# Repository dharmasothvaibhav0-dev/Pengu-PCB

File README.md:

# Pengu-PCB
Using an Astable Multivibrator to light up different LEDS automatically, the LEDS as the eyes oscillate and flash after one another (Like they are winking)

-----------------------------------------------------------------------------------------
# The Circuit

The Main components in my circuit includes 6 resistors, 2 capacitors, 2 transistors, and 8 LEDS. The circuit itself is basically an Astable multivibrator which is what causes the oscillation to occur. I originally intended to create a seperate Bistable multivibrator, however it did not work as expected so I connected the components from the bistable to create one big Astable circuit. Because of the Astable circuit type, it causes the LEDS to flash one after another in a pattern. An observation I made was that the pattern for the bottom LEDS can also swap if we were to reroute the wires to the opposite collector which was interesting to me. 

----------------------------------------------------------------------------------------------------
# The Schematic

--------------------------------------------------------------------------------------------------
# Falstad Circuit link

I created the circuit using Falstad. Feel free to try it out!

https://is.gd/EEGnGU

------------------------------------------------------------------------------------------------

# PCB Design

I chose to convert my Circuit into the design of a penguin. I used the main two LEDS part of the Astable circuit as the eyes for the penguin, and the other LEDS I attached as arms.

Front of the PCB- 

Back of the PCB-

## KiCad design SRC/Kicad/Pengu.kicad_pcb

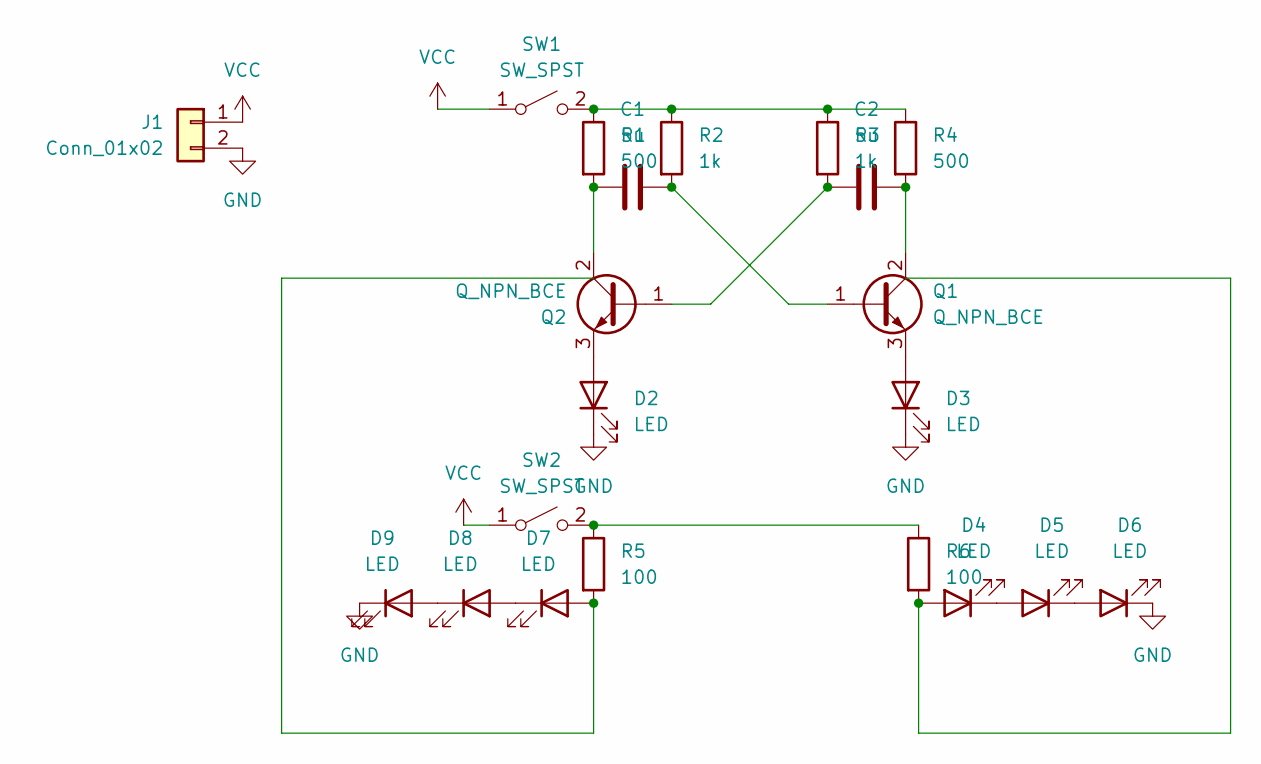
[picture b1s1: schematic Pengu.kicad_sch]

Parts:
C1, C2: 5u; C_Disc_D5.0mm_W2.5mm_P5.00mm
D2, D3, D4, D5, D6, D7, D8, D9: LED; LED_D5.0mm
J1: Conn_01x02; PinHeader_1x02_P2.54mm_Vertical
Q1, Q2: Q_NPN_BCE; TO-92L_Inline_Wide
R1, R4: 500; R_Axial_DIN0204_L3.6mm_D1.6mm_P7.62mm_Horizontal
R2, R3: 1k; R_Axial_DIN0204_L3.6mm_D1.6mm_P7.62mm_Horizontal
R5, R6: 100; R_Axial_DIN0204_L3.6mm_D1.6mm_P7.62mm_Horizontal
SW1, SW2: SW_SPST; SW_PUSH_6mm

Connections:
GND: D2.1 (K), D3.1 (K), D6.1 (K), D9.1 (K), J1.2
unnamed: D2.2 (A), Q2.3 (E)
unnamed: D3.2 (A), Q1.3 (E)
unnamed: D4.2 (A), R6.2
unnamed: D4.1 (K), D5.2 (A)
unnamed: D5.1 (K), D6.2 (A)
unnamed: D7.2 (A), R5.2
unnamed: D7.1 (K), D8.2 (A)
unnamed: D8.1 (K), D9.2 (A)
unnamed: C1.2, Q1.1 (B), R2.2
unnamed: C2.2, Q1.2 (C), R4.2
unnamed: C2.1, Q2.1 (B), R3.2
unnamed: C1.1, Q2.2 (C), R1.2
unnamed: R1.1, R2.1, R3.1, R4.1, SW1.2 (B)
unnamed: R5.1, R6.1, SW2.2 (B)
VCC: J1.1, SW1.1 (A), SW2.1 (A)

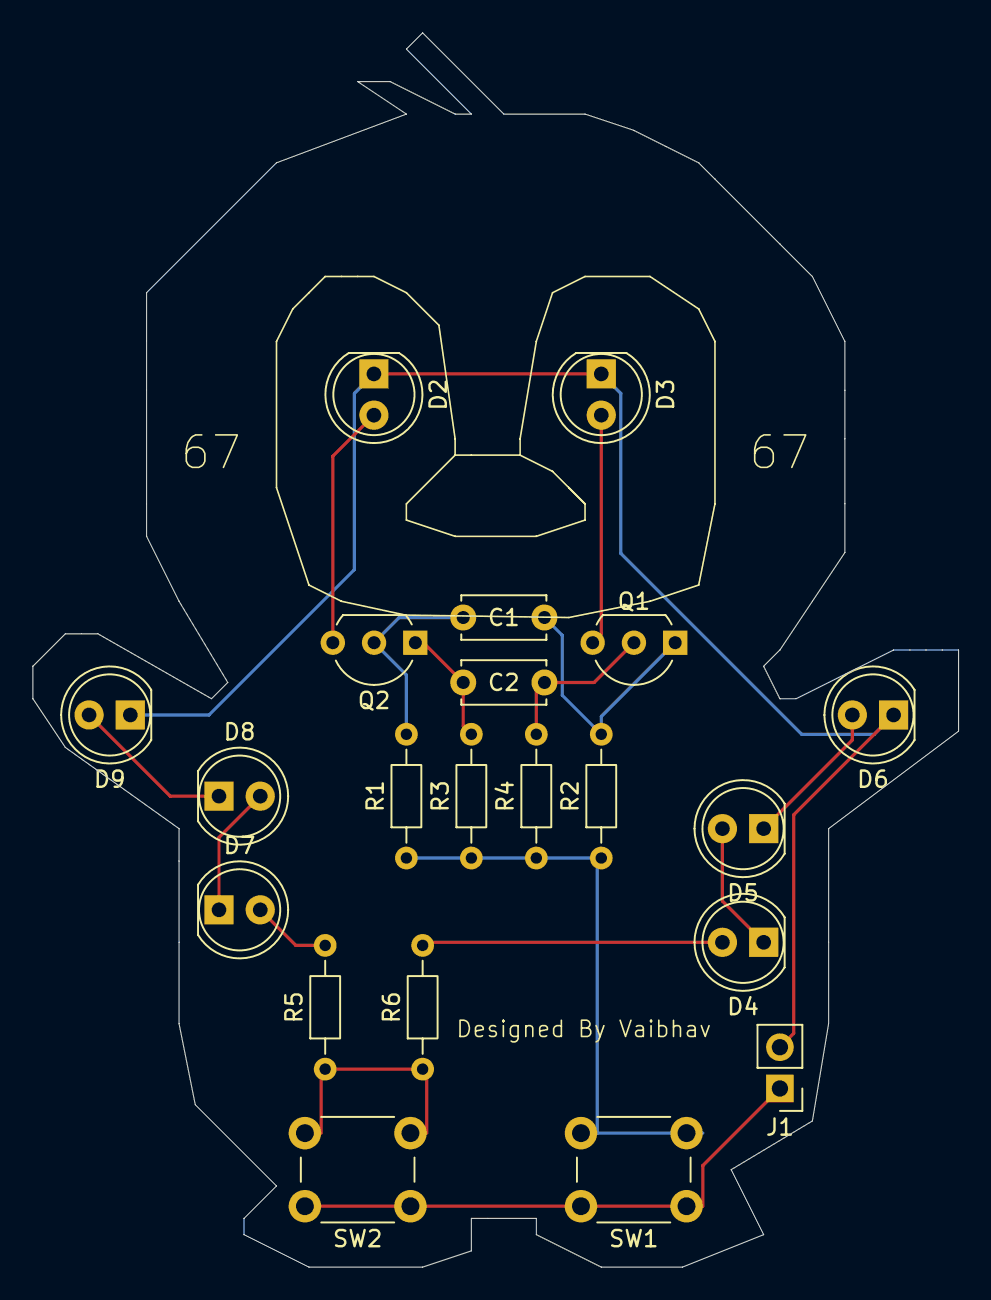
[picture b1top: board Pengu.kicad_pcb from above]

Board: 2 copper layers, 57.0 x 76.0 mm, 21 parts (0 on the bottom side), 16 nets.

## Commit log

2026-03-24 Create SRC
2026-03-25 Update README.md
    I forgot to add the schematic to the readme Oopsies
2026-03-29 Update Journal.md
    Correctly added pictures to journal
